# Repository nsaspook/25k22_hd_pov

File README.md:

# 46k22_hd_pov
HD POV demo code

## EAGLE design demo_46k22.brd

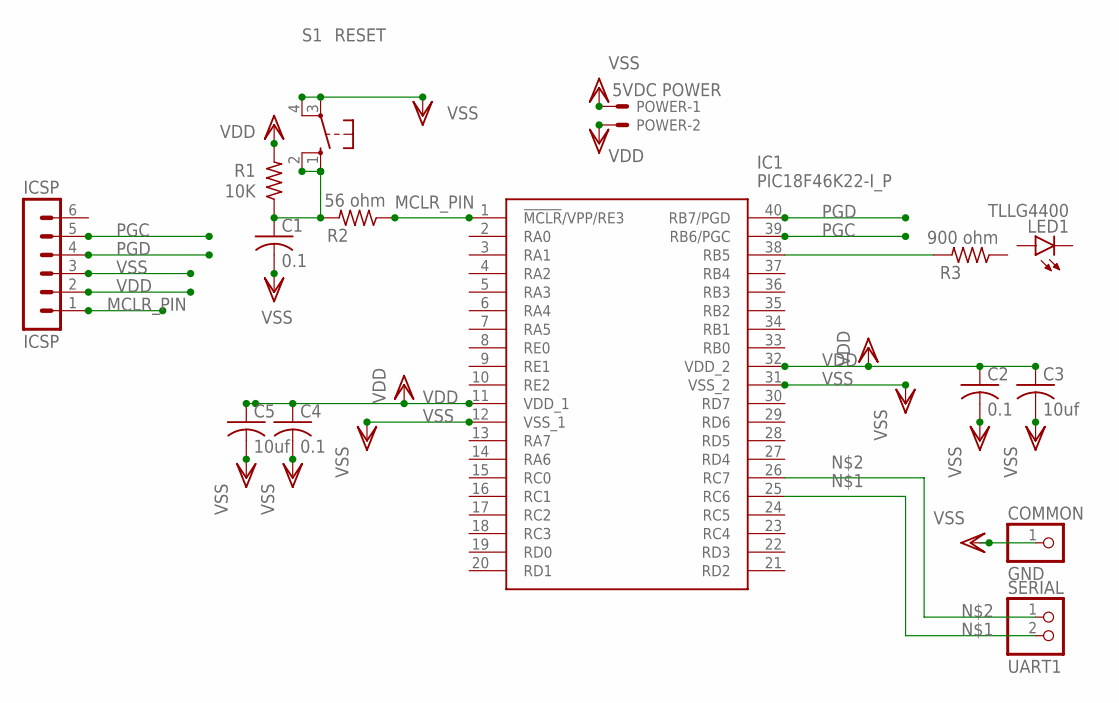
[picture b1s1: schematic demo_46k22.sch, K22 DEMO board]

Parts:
C1, C2, C4: 0.1; C025-030X050
C3, C5: 10uf; C025-030X050
COMMON: GND; 1X01
IC1: PIC18F46K22-I_P; DIP1543W58P254L5175H635Q40N
ICSP: ICSP; MA06-1
LED1: TLLG4400; LED3MM
POWER: 5VDC POWER; 22-23-2021
R1: 10K; 0204/7
R2: 56 ohm; 0204/7
R3: 900 ohm; 0204/7
S1: RESET; B3F-10XX
SERIAL: UART1; 1X02

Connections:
MCLR_PIN: IC1.1 (!MCLR!/VPP/RE3), ICSP.1, R2.1
MCLR_SW: C1.1, R1.1, R2.2, S1.1 (S), S1.2 (S1)
unnamed: IC1.25 (RC6), SERIAL.2
unnamed: IC1.26 (RC7), SERIAL.1
unnamed: IC1.38 (RB5), R3.2
PGC: IC1.39 (RB6/PGC), ICSP.5
PGD: IC1.40 (RB7/PGD), ICSP.4
VDD: C2.1, C3.1, C4.1, C5.1, IC1.11 (VDD_1), IC1.32 (VDD_2), ICSP.2, POWER.2, R1.2
VSS: C1.2, C2.2, C3.2, C4.2, C5.2, COMMON.1, IC1.12 (VSS_1), IC1.31 (VSS_2), ICSP.3, POWER.1, S1.3, S1.4 (P1)

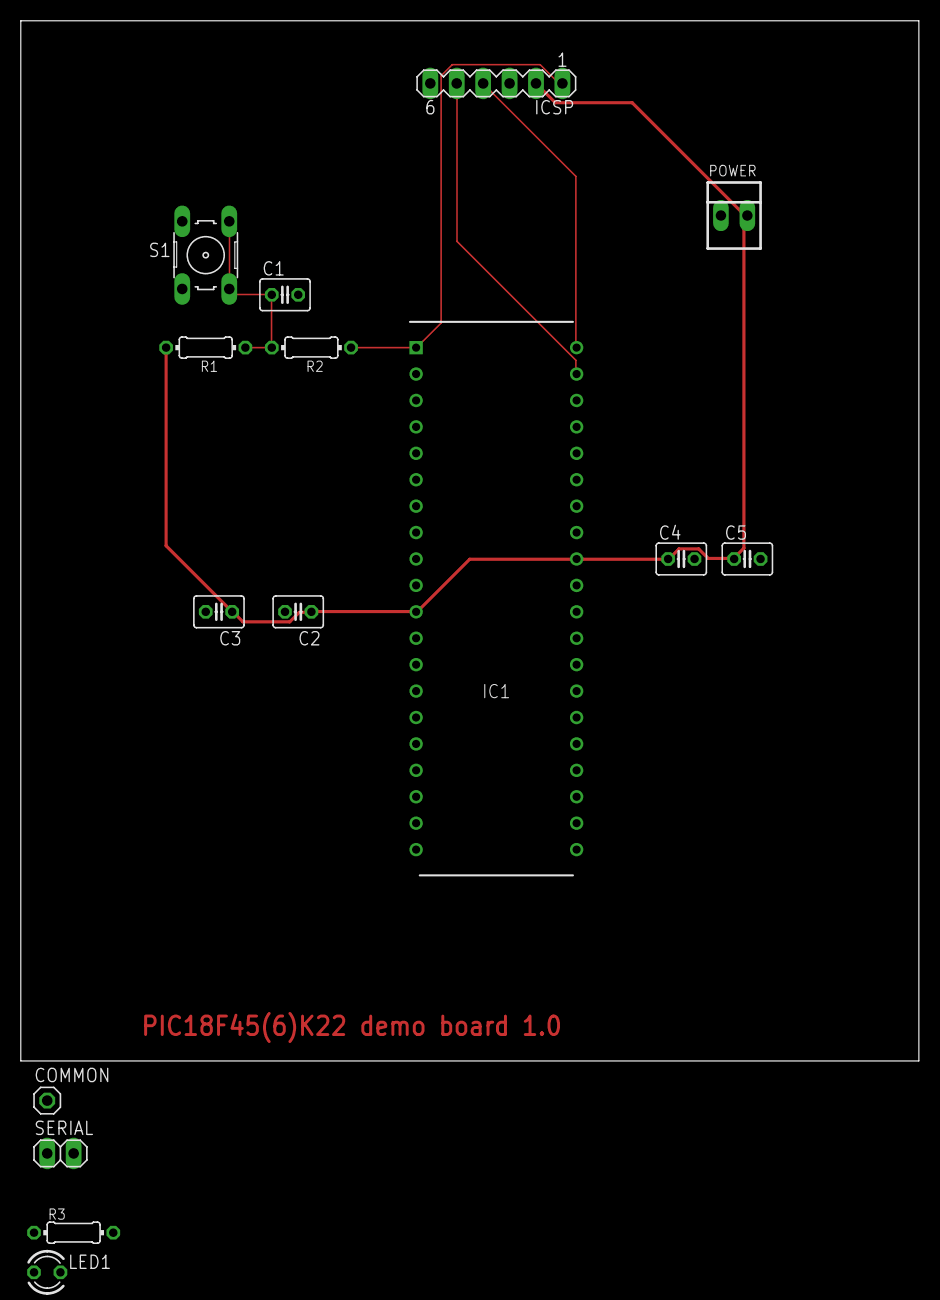
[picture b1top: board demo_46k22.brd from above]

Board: 2 copper layers, 86.3 x 100.0 mm, 15 parts (0 on the bottom side), 9 nets.

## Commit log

2023-05-05 update to modern MCC and XC8
2023-05-05 45k22 version
2023-05-05 update to 46K22 device for testing
